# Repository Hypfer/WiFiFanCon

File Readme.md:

# WiFiFanCon

Control 12V PC Fans via Wi-Fi and [Tasmota](https://github.com/arendst/Tasmota)

## Features

- Support of up to four 4-Pin PWM 12V PC Fans
- Individual RPM Monitoring for all 4 Fans
- Full control via a Webinterface
- Optional MQTT support with Home Assistant Autodiscovery utilizing [hct](https://github.com/fmtr/hct)
- Extension headers to allow for customization with e.g. additional temperature probes
- Very easy beginner-friendly THT soldering
- Fits snugly into an isolated 45ct junction box

## Where?

Head over to the [./pcb](./pcb) for the pcb.

For the firmware, install [Tasmota](https://github.com/arendst/Tasmota) e.g. using their fancy fully browser-based installer, then check out the [./berry](./berry) folder.

## Why?

I do have quite a few heat-producing devices such as servers or Hi-Fi equipment, which are trapped in whatever
furniture from Ikea barely fit them. This achieves a clean look but also kills the hardware due to insufficient ventilation.

My first solution for this was to add a few very silent 12V Noctua NF-A14 PWM PC Fans and run them at 5V with 33% duty cycle using an Arduino nano.
While that worked just fine, after a year, I've noticed quite a lot of dust buildup on the Fans as well as everything else.

Therefore, I was looking for a way to periodically run the Fans at full speed to blow away whatever dust buildup there might be.
How else would you do that if not via MQTT automated by Home Assistant?

## Pictures?

## How?

As it turns out, the ESP32 offers everything required for such a project.
It has Wi-Fi, it can do 25kHz PWM with more than 4 channels and it is also capable of monitoring the Fan speed.
Furthermore, as it is available as a full devkit PCB, flashing, soldering and everything else is very easy.

Therefore, I basically just needed to design a PCB that features a DC Jack, some Fan Headers and connects everything in a neat package.
Because it is only 70x70mm in size, it perfectly fits into these dirt-cheap german junction boxes, which you can get for 45ct each.

## Why not use something else?

While there are other projects on GitHub achieving similar things, they didn't really 100% fit my requirements, which are:

- Set Fanspeed to x%
- Don't care about temperature
- Show up in home assistant
- Be very easy to solder

## License

This hardware is licensed under the
[Creative Commons Attribution-ShareAlike 4.0 International License][cc-by-sa].

[![CC BY-SA 4.0][cc-by-sa-image]][cc-by-sa]

The software is licensed under the Apache-2.0 license.

[cc-by-sa]: http://creativecommons.org/licenses/by-sa/4.0/
[cc-by-sa-image]: ./img/cc-by-sa.png

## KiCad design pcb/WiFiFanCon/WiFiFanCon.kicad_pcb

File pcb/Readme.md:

## The Board

Gerber files can be found in the [releases section](https://github.com/Hypfer/WiFiFanCon/releases), but you can also just create them yourself using KiCAD 6

## Required parts

To build one of these you will need:

- 1x ESP32 Devkit.

  There are multiple revisions of this. make sure to get the 30-Pin one where the first pin on the left of the USB connector is labelled VIN.

- 4x 10k Resistor

- 4x 4-Pin PC Fan Header

  I used the Molex 47053-1000

- 1x DC Jack

  The board was designed with the CUI PJ-202BH in mind

- 1x 1N5817 Schottky Diode

  To protect your voltage regulator

- 1x Voltage Regulator 12v -> 5v

  I've used the RECOM R-785.0-1.0, which is very efficient and doesn't require any other components

- 0-2x 10uF 16v or similar cap

  Your voltage regulator might need those

Soldering should be straightforward and easy even for beginners.

I recommend the following order:
1. Resistors
2. Schottky
3. ESP32 Devkit
4. (Caps)
5. Fan Headers
6. DC Jack
7. Voltage Regulator

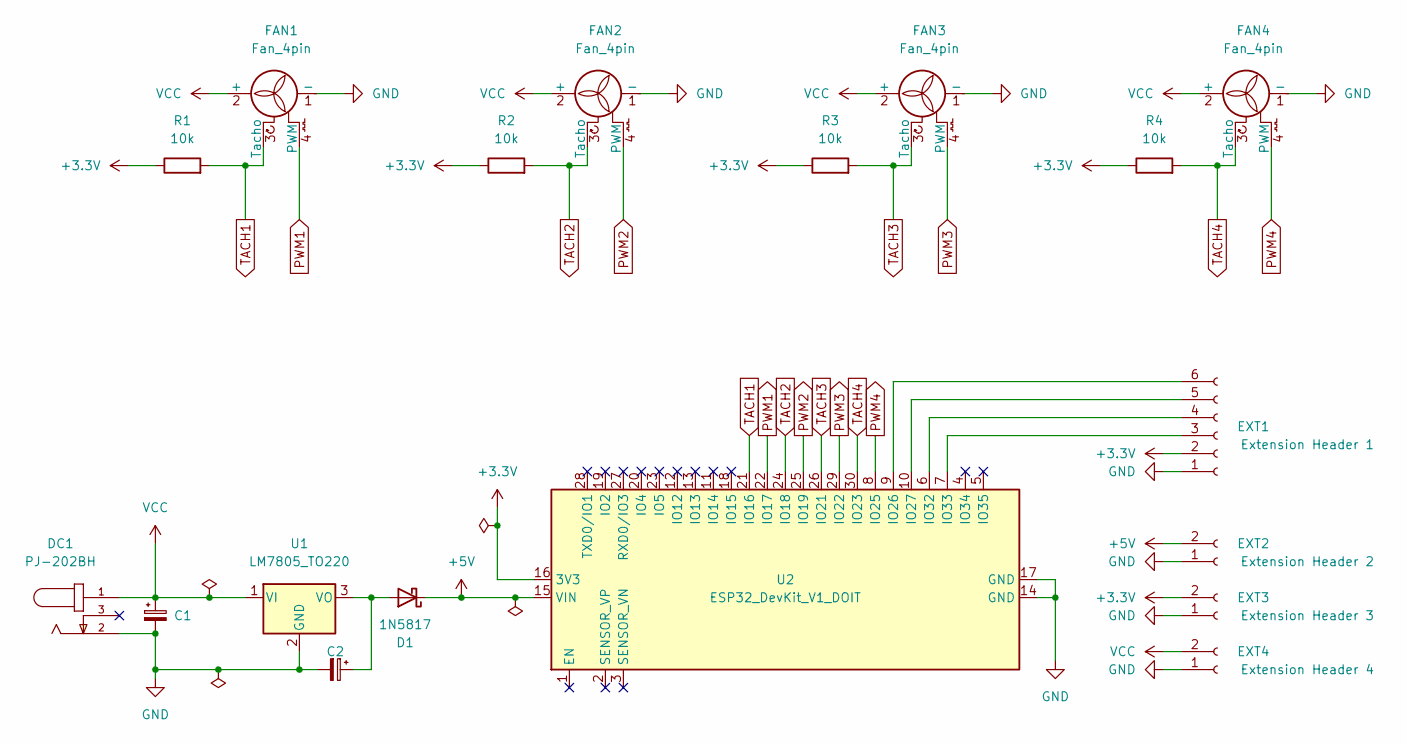
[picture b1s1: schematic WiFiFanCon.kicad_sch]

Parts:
C1, C2: C_Polarized_Small; CP_Radial_D5.0mm_P2.00mm
D1: 1N5817; D_DO-41_SOD81_P10.16mm_Horizontal
DC1: PJ-202BH; CUI_PJ-202BH; PART_REV 1.02
EXT1: Extension Header 1; PinSocket_1x06_P2.54mm_Vertical
EXT2: Extension Header 2; PinSocket_1x02_P2.54mm_Vertical
EXT3: Extension Header 3; PinSocket_1x02_P2.54mm_Vertical
EXT4: Extension Header 4; PinSocket_1x02_P2.54mm_Vertical
FAN1, FAN2, FAN3, FAN4: Fan_4pin; FanPinHeader_1x04_P2.54mm_Vertical
R1, R2, R3, R4: 10k; R_Axial_DIN0207_L6.3mm_D2.5mm_P10.16mm_Horizontal
U1: LM7805_TO220; TO-220-3_Vertical
U2: ESP32_DevKit_V1_DOIT; esp32_devkit_v1_doit

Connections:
+3V3: EXT1.2, EXT3.2, R1.1, R2.1, R3.1, R4.1, U2.16 (3V3)
+5V: D1.1 (K), EXT2.2, U2.15 (VIN)
GND: C1.2, C2.2, DC1.2, EXT1.1, EXT2.1, EXT3.1, EXT4.1, FAN1.1 (-), FAN2.1 (-), FAN3.1 (-), FAN4.1 (-), U1.2 (GND), U2.14 (GND), U2.17 (GND)
unnamed: C2.1, D1.2 (A), U1.3 (VO)
unnamed: EXT1.3, U2.7 (IO33)
unnamed: EXT1.4, U2.6 (IO32)
unnamed: EXT1.5, U2.10 (IO27)
unnamed: EXT1.6, U2.9 (IO26)
PWM1: FAN1.4 (PWM), U2.22 (IO17)
PWM2: FAN2.4 (PWM), U2.25 (IO19)
PWM3: FAN3.4 (PWM), U2.29 (IO22)
PWM4: FAN4.4 (PWM), U2.8 (IO25)
TACH1: FAN1.3 (Tacho), R1.2, U2.21 (IO16)
TACH2: FAN2.3 (Tacho), R2.2, U2.24 (IO18)
TACH3: FAN3.3 (Tacho), R3.2, U2.26 (IO21)
TACH4: FAN4.3 (Tacho), R4.2, U2.30 (IO23)
VCC: C1.1, DC1.1, EXT4.2, FAN1.2 (+), FAN2.2 (+), FAN3.2 (+), FAN4.2 (+), U1.1 (VI)

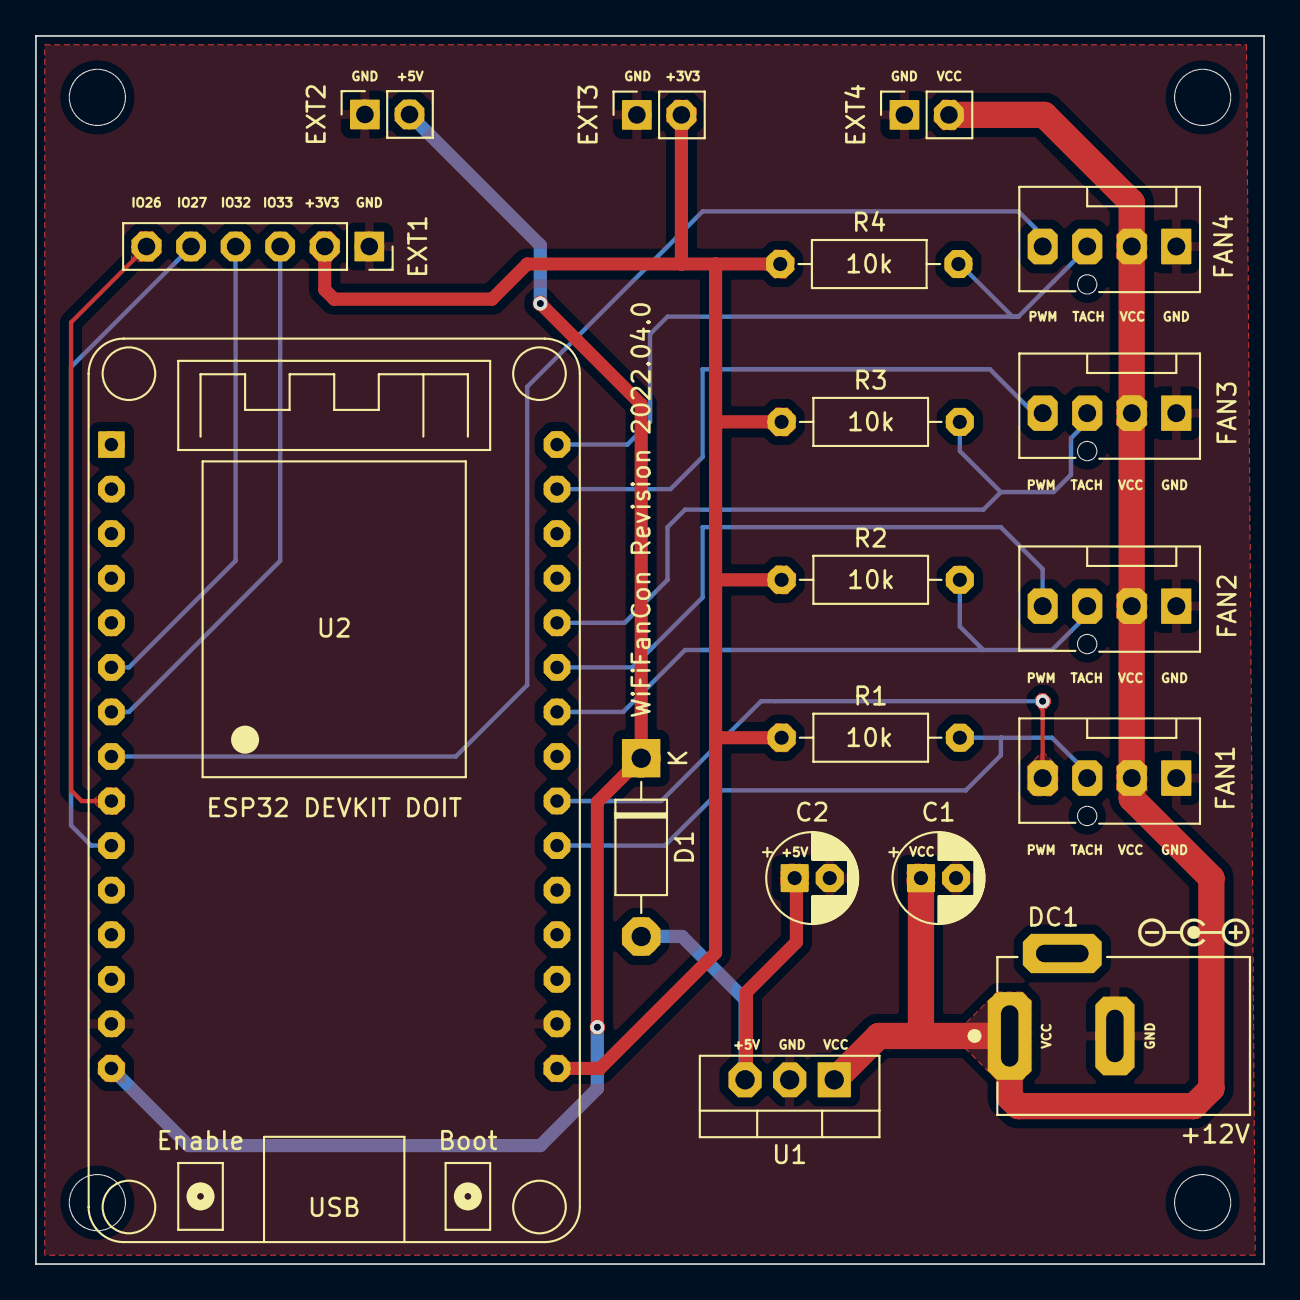
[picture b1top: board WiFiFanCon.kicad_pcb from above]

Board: 2 copper layers, 70.0 x 70.0 mm, 18 parts (0 on the bottom side), 17 nets.

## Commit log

2022-04-23 Initial github import
2022-04-23 Add render
2023-07-01 Berry rewrite
2023-07-11 Fix multi-fan usage
2024-08-22 Calculate RPM more accurately and independently of timer interval
    - Calculate actual RPM based on time and pulse delta since last update.
    - Eliminates the need to reset the pulse counter after each update..
2024-08-25 Calculate RPM more accurately and independently of timer interval (#1)
    - Calculate actual RPM based on time and pulse delta since last update.
    - Eliminates the need to reset the pulse counter after each update..
